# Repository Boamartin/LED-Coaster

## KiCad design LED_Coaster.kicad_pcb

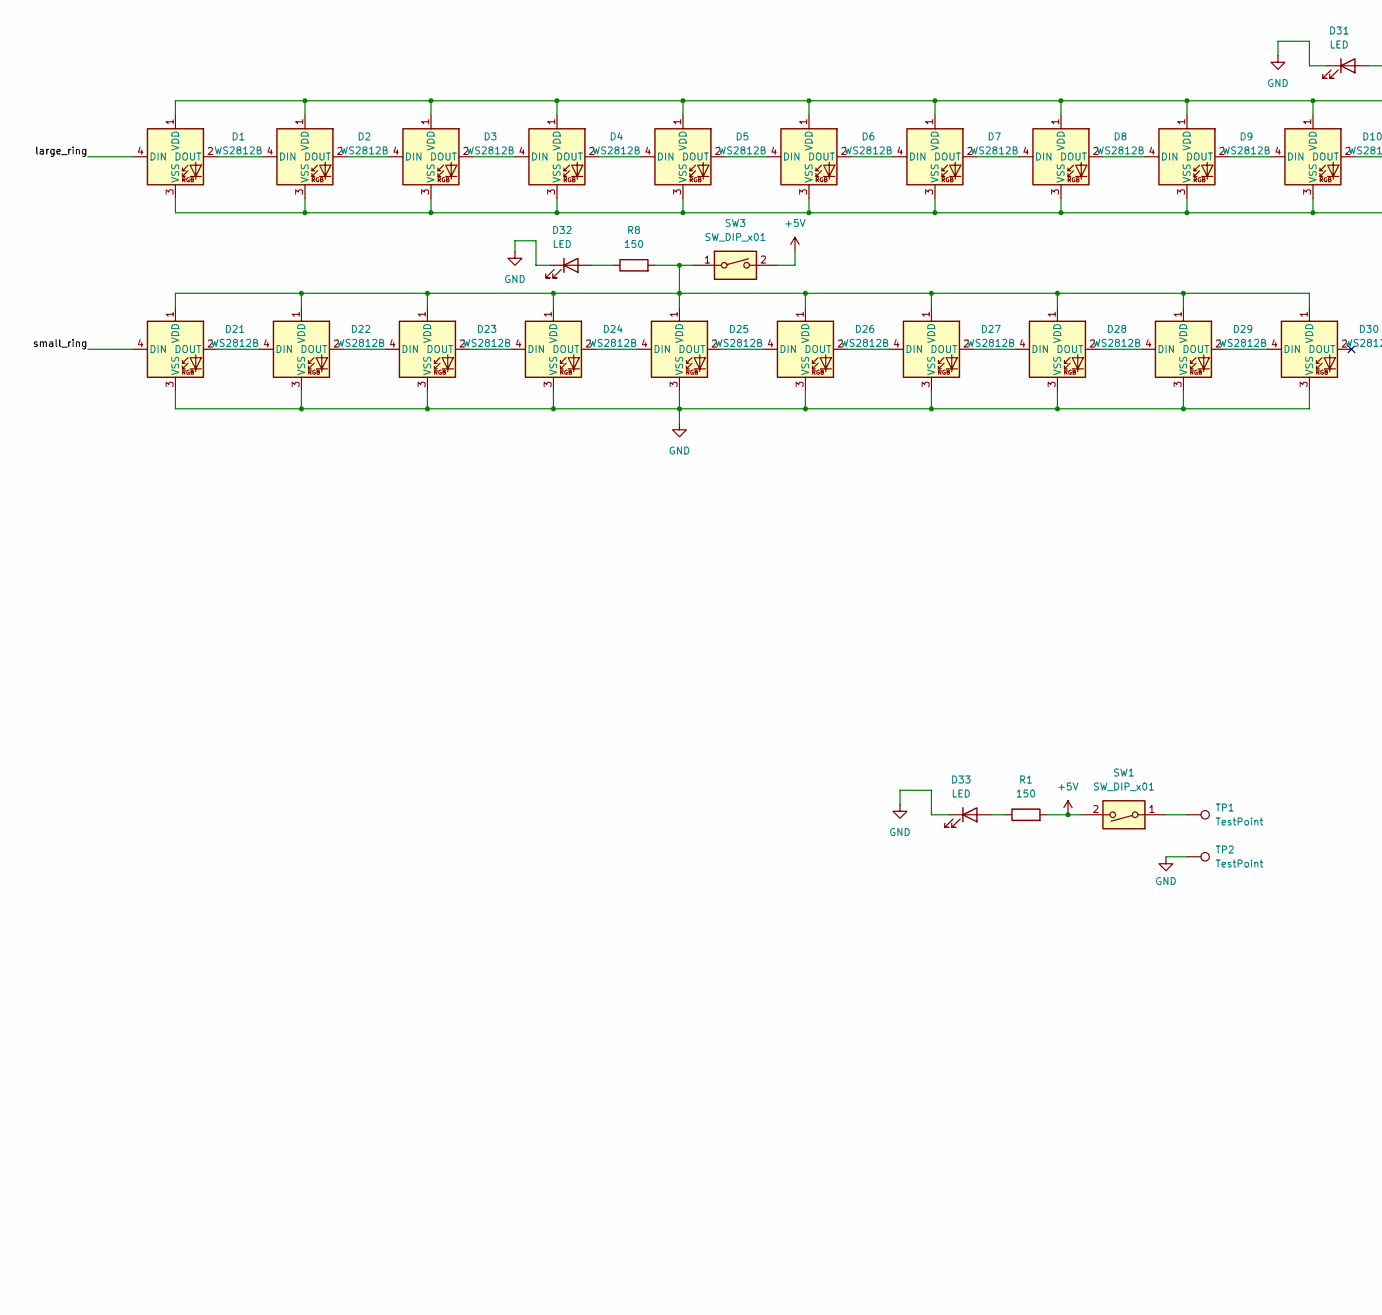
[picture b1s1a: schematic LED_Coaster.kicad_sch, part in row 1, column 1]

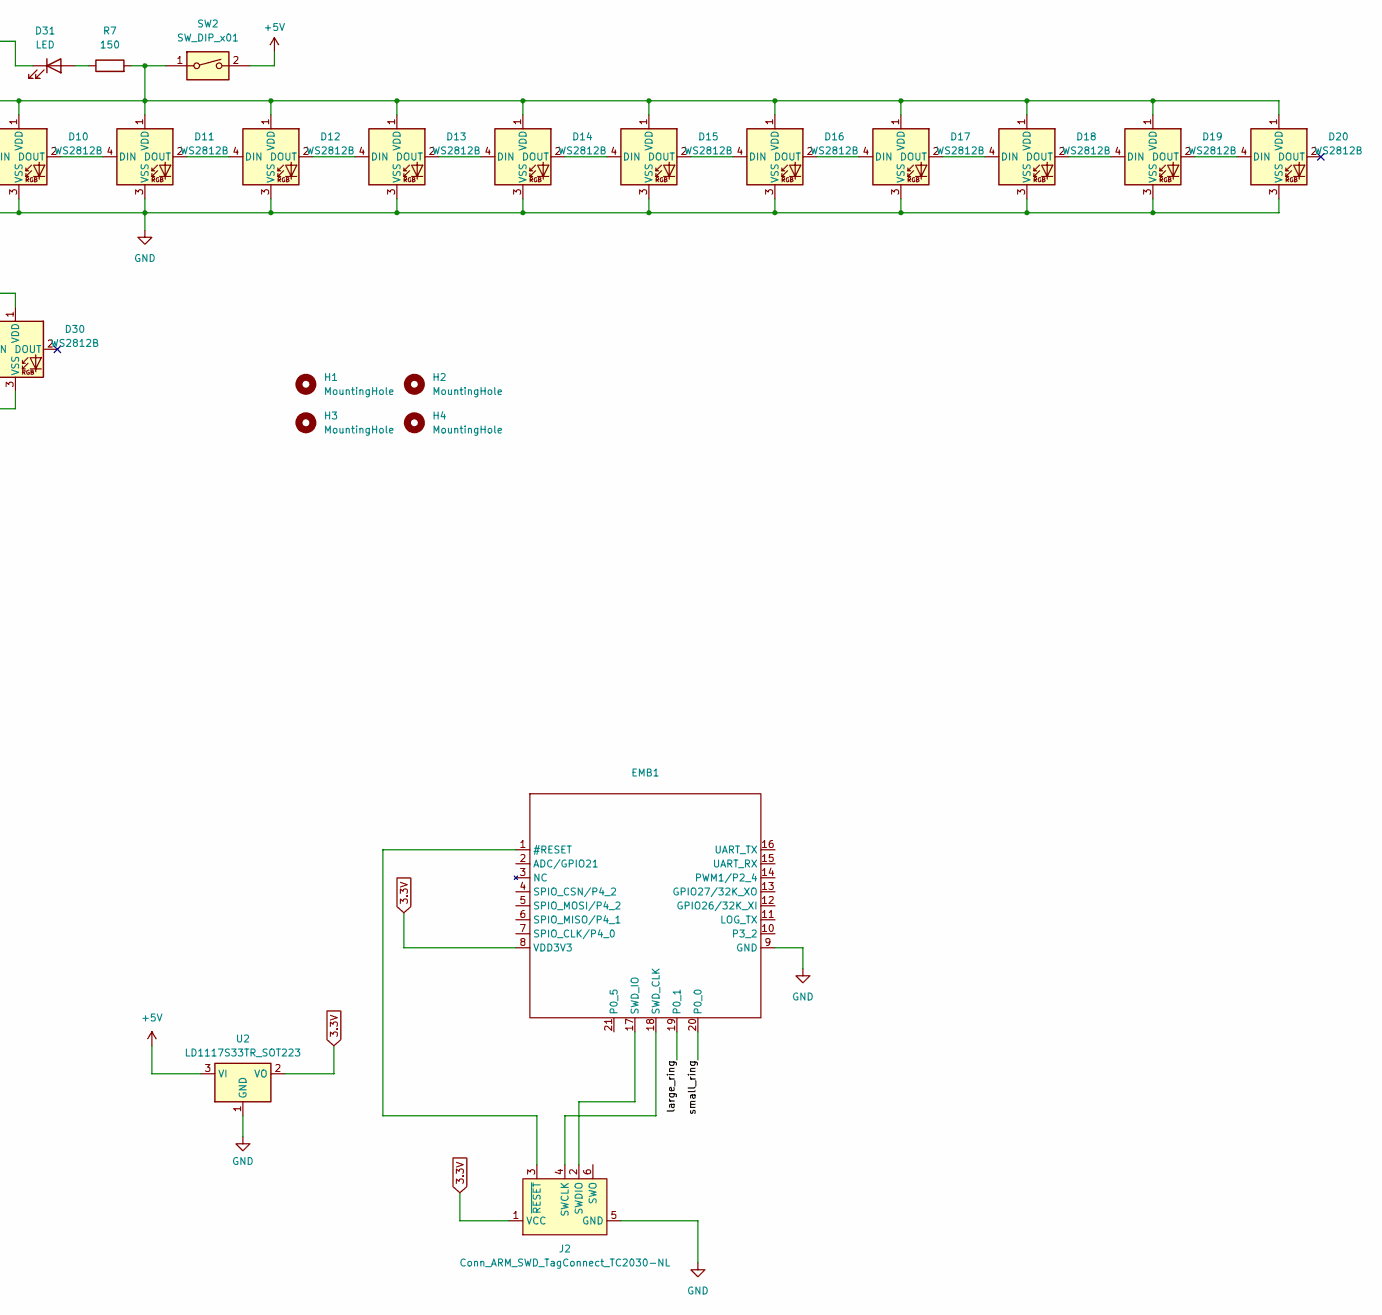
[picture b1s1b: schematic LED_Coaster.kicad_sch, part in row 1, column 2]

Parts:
D1, D2, D3, D4, D5, D6, D7, D8, D9, D10, D11, D12, D13, D14, D15, D16, D17, D18, D19, D20, D21, D22, D23, D24, D25, D26, D27, D28, D29, D30: WS2812B; LED_WS2812B_PLCC4_5.0x5.0mm_P3.2mm
D31, D32, D33: LED; LED_0805_2012Metric_Pad1.15x1.40mm_HandSolder
EMB1: EMB1082
H1, H2, H3, H4: MountingHole; MountingHole_4.3mm_M4_Pad_Via
J2: Conn_ARM_SWD_TagConnect_TC2030-NL; Tag-Connect_TC2030-IDC-NL_2x03_P1.27mm_Vertical
R1, R7, R8: 150; R_0805_2012Metric_Pad1.20x1.40mm_HandSolder
SW1, SW2, SW3: SW_DIP_x01; SW_SPDT_PCM12
TP1, TP2: TestPoint; TestPoint_Loop_D1.80mm_Drill1.0mm_Beaded
U2: LD1117S33TR_SOT223; SOT-223-3_TabPin2

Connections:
3.3V: EMB1.8 (VDD3V3), J2.1 (VCC), U2.2 (VO)
+5V: R1.2, SW1.2, SW2.2, SW3.2, U2.3 (VI); also elsewhere on the board
/large_ring: D1.4 (DIN), EMB1.19 (P0_1)
/small_ring: D21.4 (DIN), EMB1.20 (P0_0)
GND: D1.3 (VSS), D2.3 (VSS), D3.3 (VSS), D4.3 (VSS), D5.3 (VSS), D6.3 (VSS), D7.3 (VSS), D8.3 (VSS), D9.3 (VSS), D10.3 (VSS), D11.3 (VSS), D12.3 (VSS), D13.3 (VSS), D14.3 (VSS), D15.3 (VSS), D16.3 (VSS), D17.3 (VSS), D18.3 (VSS), D19.3 (VSS), D20.3 (VSS), D21.3 (VSS), D22.3 (VSS), D23.3 (VSS), D24.3 (VSS), D25.3 (VSS), D26.3 (VSS), D27.3 (VSS), D28.3 (VSS), D29.3 (VSS), D30.3 (VSS), D31.1 (K), D32.1 (K), D33.1 (K), EMB1.9 (GND), J2.5 (GND), TP2.1, U2.1 (GND); also elsewhere on the board
unnamed: D1.2 (DOUT), D2.4 (DIN)
unnamed: D1.1 (VDD), D2.1 (VDD), D3.1 (VDD), D4.1 (VDD), D5.1 (VDD), D6.1 (VDD), D7.1 (VDD), D8.1 (VDD), D9.1 (VDD), D10.1 (VDD), D11.1 (VDD), D12.1 (VDD), D13.1 (VDD), D14.1 (VDD), D15.1 (VDD), D16.1 (VDD), D17.1 (VDD), D18.1 (VDD), D19.1 (VDD), D20.1 (VDD), R7.2, SW2.1
unnamed: D2.2 (DOUT), D3.4 (DIN)
unnamed: D3.2 (DOUT), D4.4 (DIN)
unnamed: D4.2 (DOUT), D5.4 (DIN)
unnamed: D5.2 (DOUT), D6.4 (DIN)
unnamed: D6.2 (DOUT), D7.4 (DIN)
unnamed: D7.2 (DOUT), D8.4 (DIN)
unnamed: D8.2 (DOUT), D9.4 (DIN)
unnamed: D9.2 (DOUT), D10.4 (DIN)
unnamed: D10.2 (DOUT), D11.4 (DIN)
unnamed: D11.2 (DOUT), D12.4 (DIN)
unnamed: D12.2 (DOUT), D13.4 (DIN)
unnamed: D13.2 (DOUT), D14.4 (DIN)
unnamed: D14.2 (DOUT), D15.4 (DIN)
unnamed: D15.2 (DOUT), D16.4 (DIN)
unnamed: D16.2 (DOUT), D17.4 (DIN)
unnamed: D17.2 (DOUT), D18.4 (DIN)
unnamed: D18.2 (DOUT), D19.4 (DIN)
unnamed: D19.2 (DOUT), D20.4 (DIN)
unnamed: D21.2 (DOUT), D22.4 (DIN)
unnamed: D21.1 (VDD), D22.1 (VDD), D23.1 (VDD), D24.1 (VDD), D25.1 (VDD), D26.1 (VDD), D27.1 (VDD), D28.1 (VDD), D29.1 (VDD), D30.1 (VDD), R8.2, SW3.1
unnamed: D22.2 (DOUT), D23.4 (DIN)
unnamed: D23.2 (DOUT), D24.4 (DIN)
unnamed: D24.2 (DOUT), D25.4 (DIN)
unnamed: D25.2 (DOUT), D26.4 (DIN)
unnamed: D26.2 (DOUT), D27.4 (DIN)
unnamed: D27.2 (DOUT), D28.4 (DIN)
unnamed: D28.2 (DOUT), D29.4 (DIN)
unnamed: D29.2 (DOUT), D30.4 (DIN)
unnamed: D31.2 (A), R7.1
unnamed: D32.2 (A), R8.1
unnamed: D33.2 (A), R1.1
unnamed: EMB1.1 (#RESET), J2.3 (~RESET)
unnamed: EMB1.18 (SWD_CLK), J2.4 (SWCLK)
unnamed: EMB1.17 (SWD_IO), J2.2 (SWDIO)
unnamed 41: SW1.1, TP1.1; also elsewhere on the board

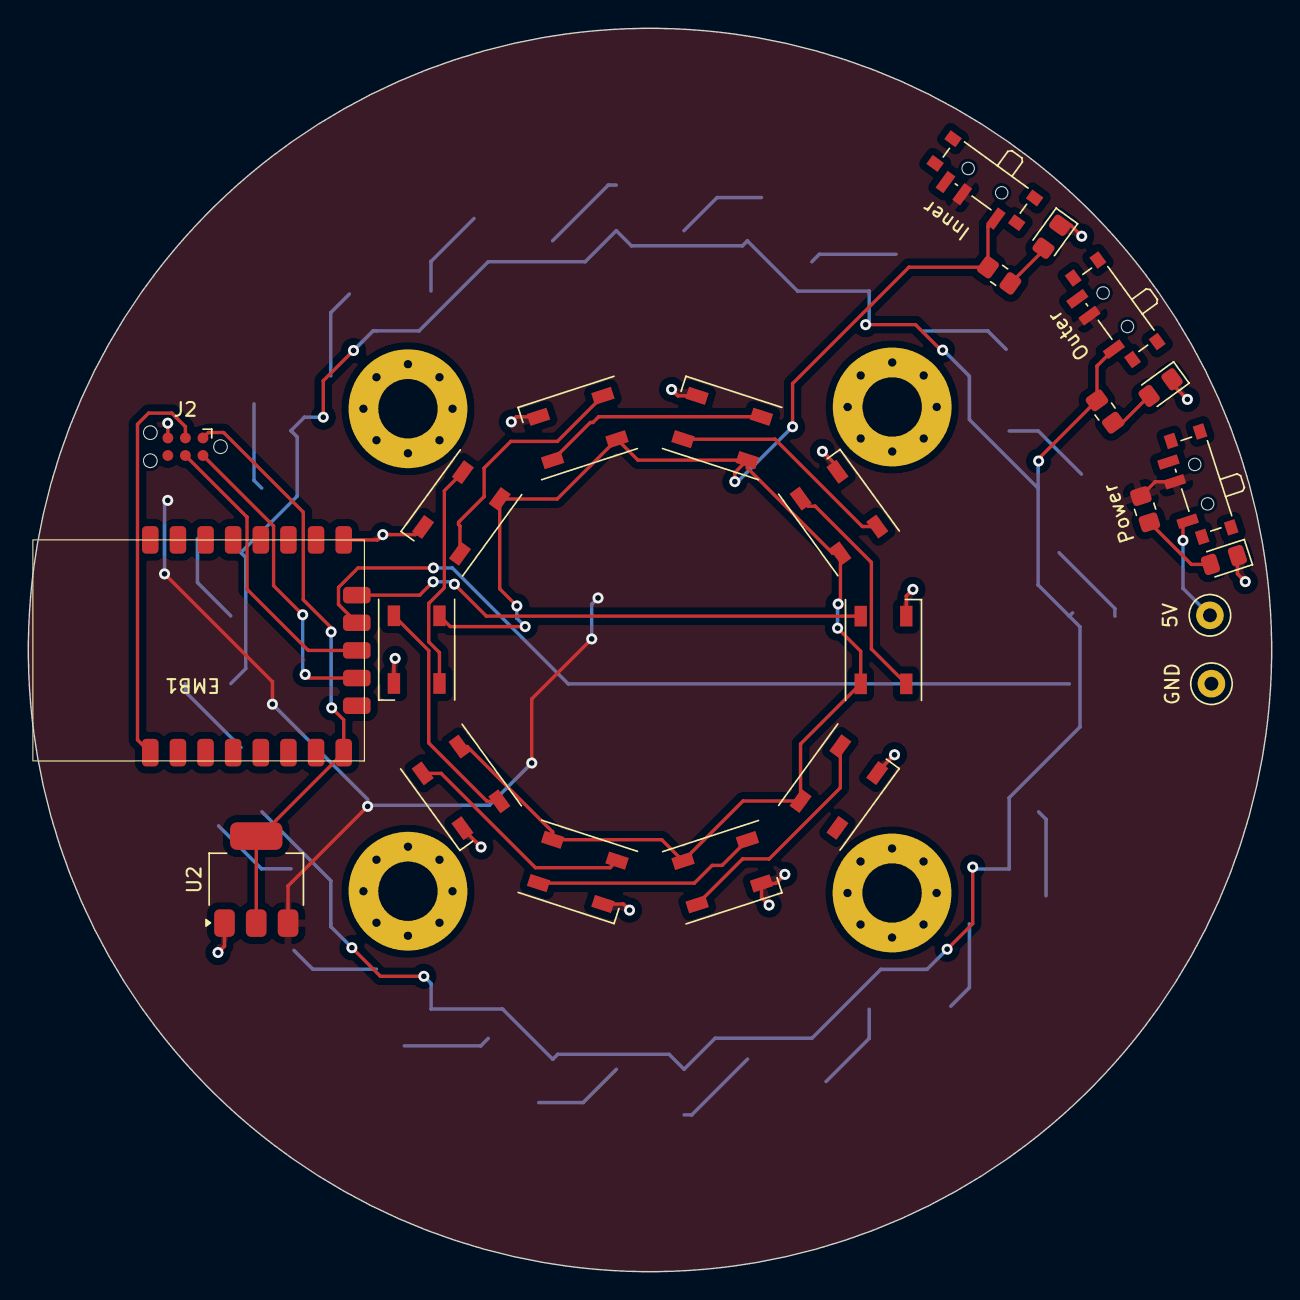
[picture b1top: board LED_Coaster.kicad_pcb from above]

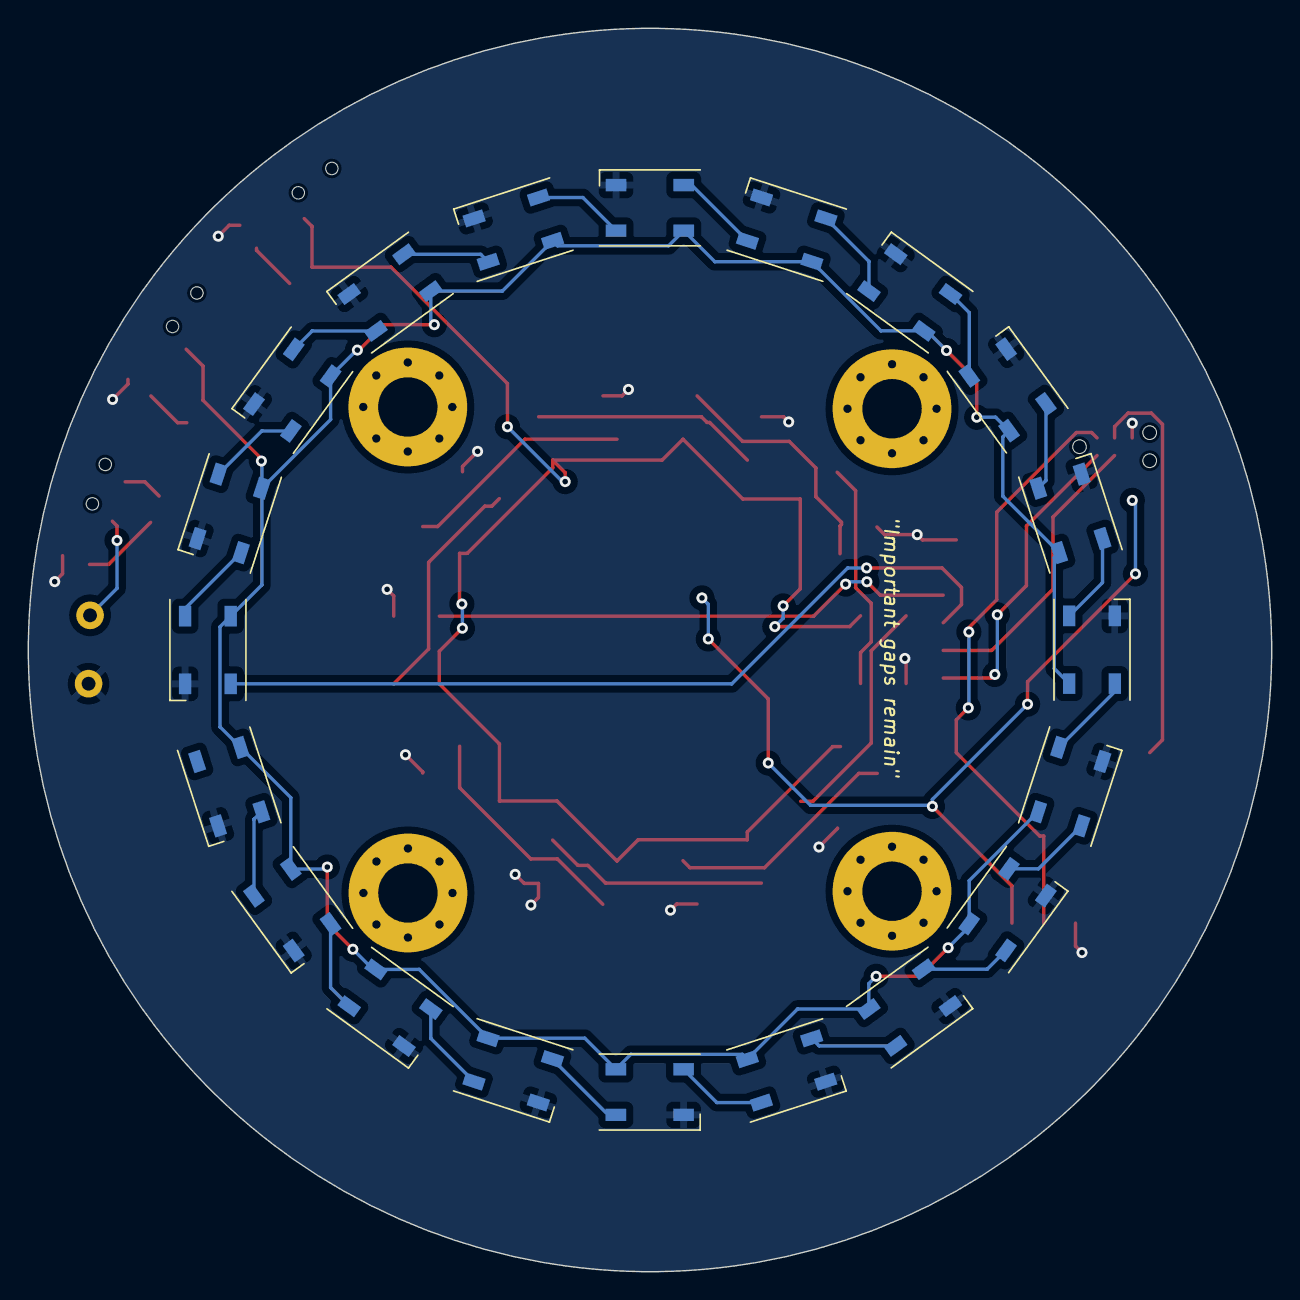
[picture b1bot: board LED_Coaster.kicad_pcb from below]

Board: 2 copper layers, 90.0 x 90.0 mm, 48 parts (20 on the bottom side), 42 nets.

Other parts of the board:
5V: TestPoint; TestPoint_Loop_D1.80mm_Drill1.0mm_Beaded
GND: TestPoint; TestPoint_Loop_D1.80mm_Drill1.0mm_Beaded
Power: SW_DIP_x01; SW_SPDT_PCM12

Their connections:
+5V: Power.2; also elsewhere on the board
GND: GND.1; also elsewhere on the board
unnamed 41: 5V.1, Power.1; also elsewhere on the board

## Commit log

2024-05-13 processor SDK
2024-05-14 Added symbol and footprint for EMB1082
2024-05-14 Added more components
2024-05-17 Added traces for EMB1082 and power switch
2024-05-23 ny kod för att testa modes
2024-06-03 updated Kicad files and test _proj
2024-06-03 jlink log
2024-06-03 Added output_led_version_2
2024-06-03 changed Readmode
2024-06-03 ARM v5 installer
